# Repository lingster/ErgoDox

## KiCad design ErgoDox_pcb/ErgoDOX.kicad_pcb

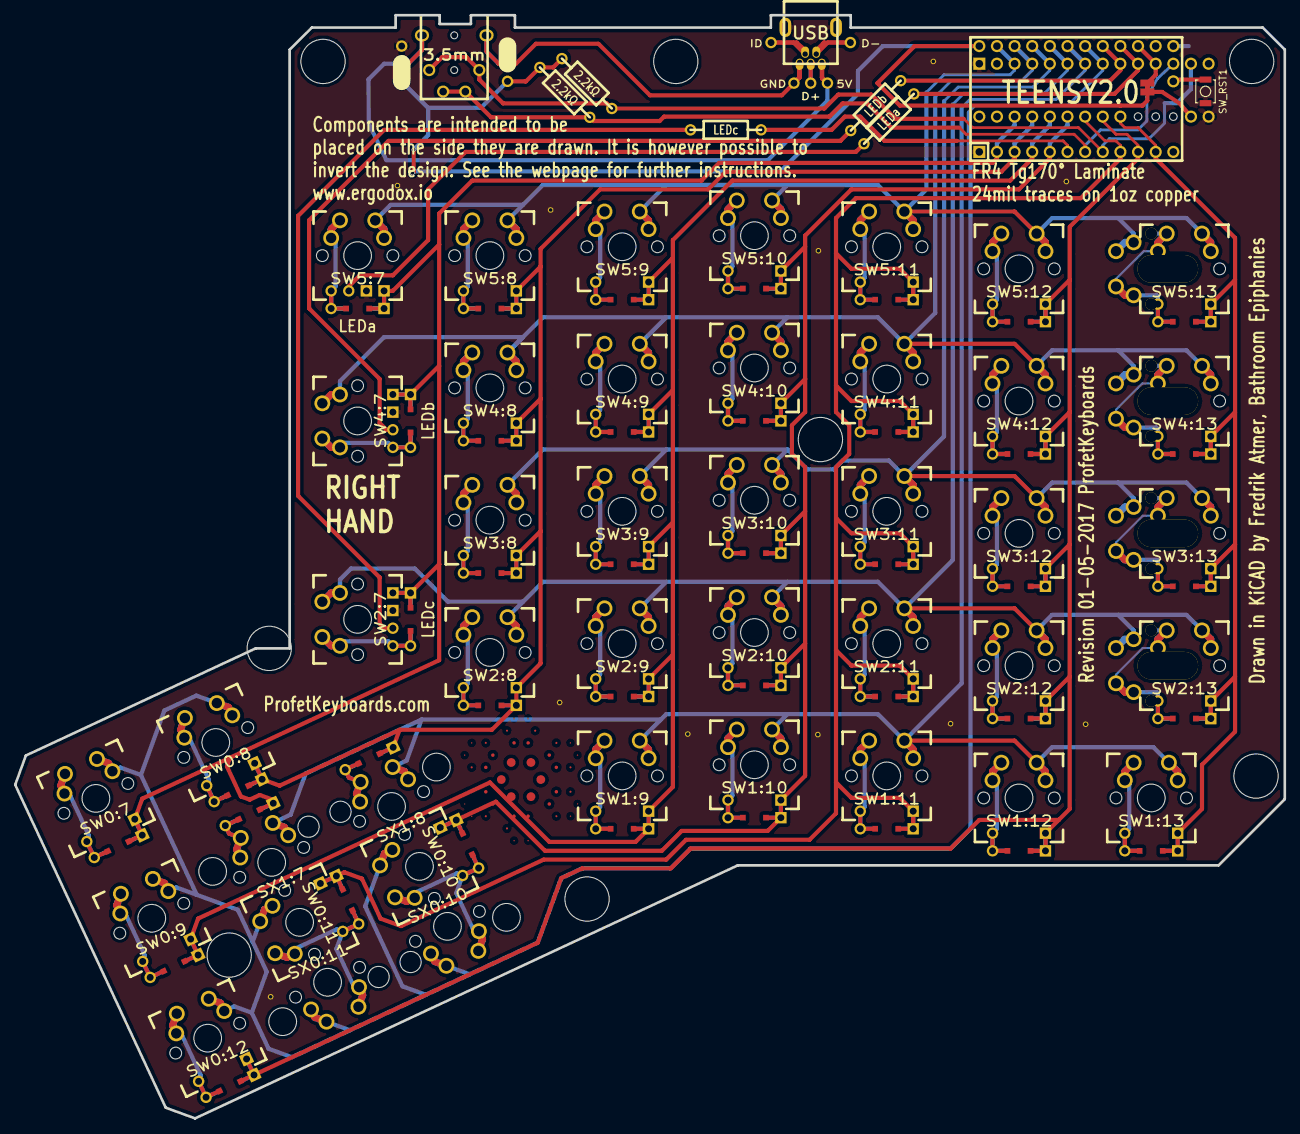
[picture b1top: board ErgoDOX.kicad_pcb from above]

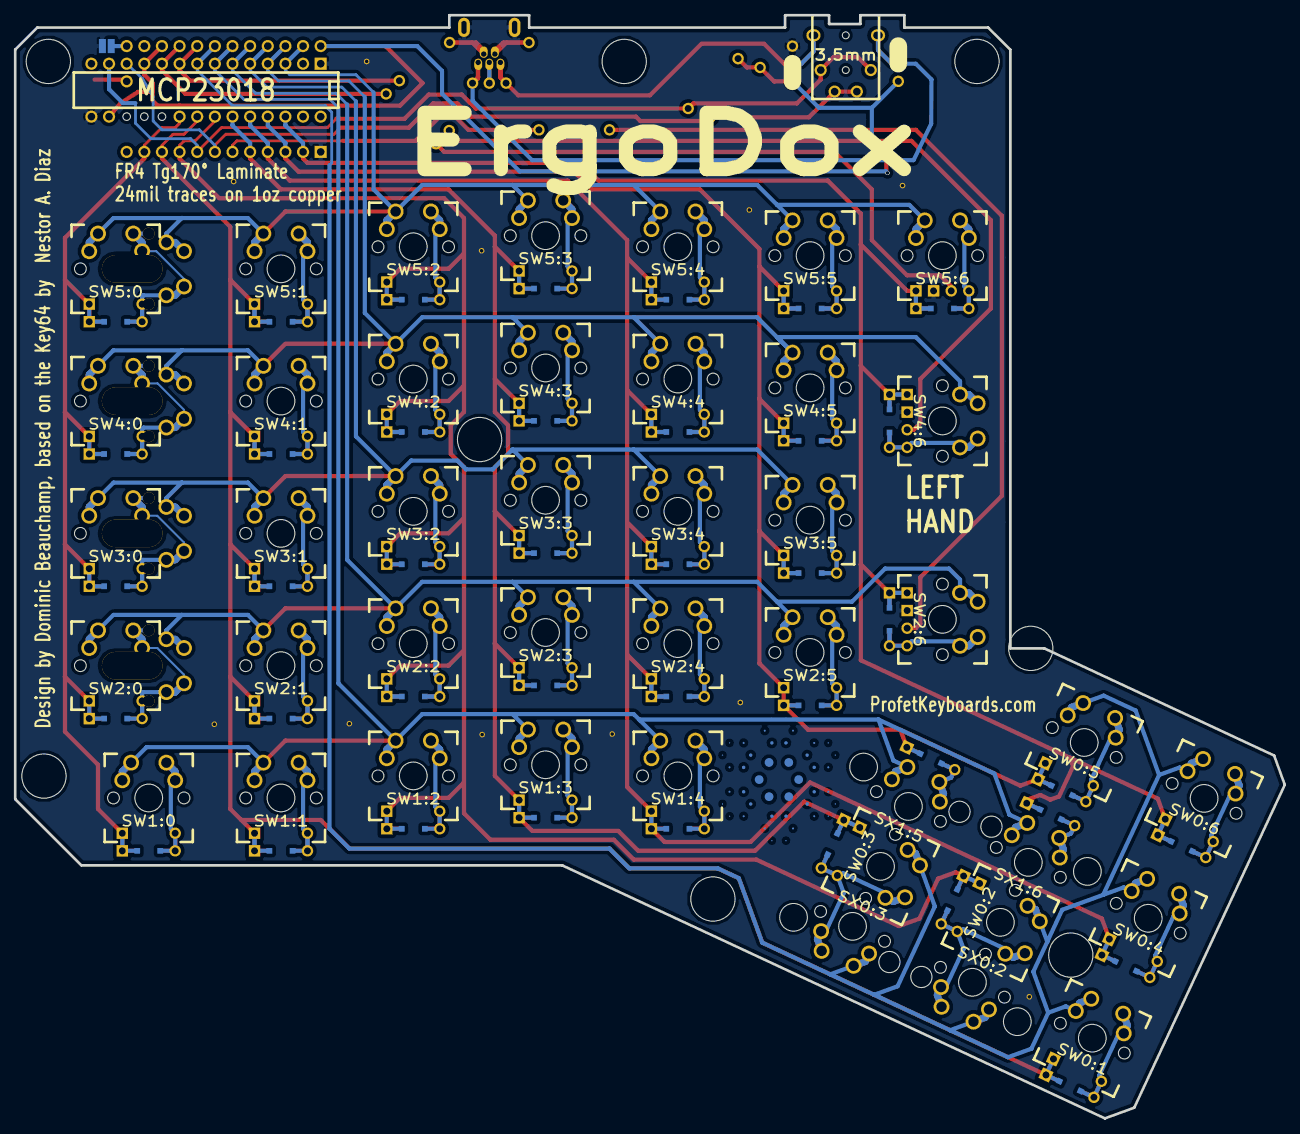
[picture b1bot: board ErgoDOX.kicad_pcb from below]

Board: 2 copper layers, 182.8 x 158.9 mm, 77 parts (4 on the bottom side), 66 nets.

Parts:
D1:7, D1:8: D; DIODE
H99: MECHANICAL; ErgoDOXmech
J1: USB; USBMINImod
J2: 3.5mm; 4pin35mmAudio
J3, J4: JMP; 100PITCH1X3
JP1, JP2: JUMPER; GAP
LED_A1: LEDa; MX_LED
LED_B1: LEDb; MX_LED
LED_C1: LEDc; MX_LED
R1, R2: 2.2kΩ; RESISTOR
RA1: LEDa; RESISTOR
RB1: LEDb; RESISTOR
RC1: LEDc; RESISTOR
S1, S2: STAB200; STAB_PCB940
STAR_1: STAR_FRONT; STAR
STAR_2: STAR_BACK; STAR
STITCHING_VIA: STITCHING_VIA
STITCHING_VIA#2, STITCHING_VIA#3, STITCHING_VIA#4, STITCHING_VIA#5, STITCHING_VIA#6, STITCHING_VIA#7, STITCHING_VIA#8, STITCHING_VIA#9, STITCHING_VIA#10, STITCHING_VIA#11: STITCHING_VIA
SW0:7: SW0:6; MX_FLIP_DIODE
SW0:8: SW0:5; MX_FLIP_DIODE
SW0:9: SW0:4; MX_FLIP_DIODE
SW0:10: SW0:3; MX_FLIP_DIODE
SW0:11: SW0:2; MX_FLIP_DIODE
SW0:12: SW0:1; MX_FLIP_DIODE
SW1:9: SW1:4; MX_FLIP_DIODE
SW1:10: SW1:3; MX_FLIP_DIODE
SW1:11: SW1:2; MX_FLIP_DIODE
SW1:12: SW1:1; MX_FLIP_DIODE
SW1:13: SW1:0; MX_FLIP_DIODE
SW2:7: SW2:6; MX_FLIP_DIODE
SW2:8: SW2:5; MX_FLIP_DIODE
SW2:9: SW2:4; MX_FLIP_DIODE
SW2:10: SW2:3; MX_FLIP_DIODE
SW2:11: SW2:2; MX_FLIP_DIODE
SW2:12: SW2:1; MX_FLIP_DIODE
SW2:13: SW2:0; MX_FLIP_XX
SW3:8: SW3:5; MX_FLIP_DIODE
SW3:9: SW3:4; MX_FLIP_DIODE
SW3:10: SW3:3; MX_FLIP_DIODE
SW3:11: SW3:2; MX_FLIP_DIODE
SW3:12: SW3:1; MX_FLIP_DIODE
SW3:13: SW3:0; MX_FLIP_XX
SW4:7: SW4:6; MX_FLIP_DIODE
SW4:8: SW4:5; MX_FLIP_DIODE
SW4:9: SW4:4; MX_FLIP_DIODE
SW4:10: SW4:3; MX_FLIP_DIODE
SW4:11: SW4:2; MX_FLIP_DIODE
SW4:12: SW4:1; MX_FLIP_DIODE
SW4:13: SW4:0; MX_FLIP_XX
SW5:7: SW5:6; MX_FLIP_DIODE
SW5:8: SW5:5; MX_FLIP_DIODE
SW5:9: SW5:4; MX_FLIP_DIODE
SW5:10: SW5:3; MX_FLIP_DIODE
SW5:11: SW5:2; MX_FLIP_DIODE
SW5:12: SW5:1; MX_FLIP_DIODE
SW5:13: SW5:0; MX_FLIP_XX
SW_RST1: SWITCH_PUSH; SW_SPST_B3U-1000P
SX0:10: SX0:3; MX_FLIP
SX0:11: SX0:2; MX_FLIP
SX1:7: SX1:6; MX_FLIP
SX1:8: SX1:5; MX_FLIP
U1: TEENSY2.0; TEENSY_2.0_WITH_RESET
U2: MCP23018; DIP28_300

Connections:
/COL0: SW1:13.4, SW2:13.4, SW3:13.4, SW4:13.4, SW5:13.4, U1.11, U2.20
/COL1: SW0:12.4, SW1:12.4, SW2:12.4, SW3:12.4, SW4:12.4, SW5:12.4, U1.10, U2.21
/COL4: SW0:9.4, SW1:9.4, SW2:9.4, SW3:9.4, SW4:9.4, SW5:9.4, U1.4, U2.24
/COL5: D1:8.2, SW0:8.4, SW2:8.4, SW3:8.4, SW4:8.4, SW5:8.4, U1.3, U2.25
/COL6: D1:7.2, SW0:7.4, SW2:7.4, SW4:7.4, SW5:7.4, U1.2, U2.26
/COL10: SW0:10.4, SW1:10.4, SW2:10.4, SW3:10.4, SW4:10.4, SW5:10.4, U1.5, U2.23
/COL11: SW0:11.4, SW1:11.4, SW2:11.4, SW3:11.4, SW4:11.4, SW5:11.4, U1.9, U2.22
/LED_A: RA1.1, U1.21, U2.10
/LED_B: RB1.1, U1.22, U2.9
/LED_C: RC1.1, U1.6
/ROW0: SW0:7.1, SW0:8.1, SW0:9.1, SW0:10.1, SW0:11.1, SW0:12.1, SX0:10.1, SX0:11.1, U1.23, U2.8
/ROW1: SW1:9.1, SW1:10.1, SW1:11.1, SW1:12.1, SW1:13.1, SX1:7.1, SX1:8.1, U1.24, U2.7
/ROW2: SW2:7.1, SW2:8.1, SW2:9.1, SW2:10.1, SW2:11.1, SW2:12.1, SW2:13.1, U1.25, U2.6
/ROW3: SW3:8.1, SW3:9.1, SW3:10.1, SW3:11.1, SW3:12.1, SW3:13.1, U1.26, U2.5
/ROW4: SW4:7.1, SW4:8.1, SW4:9.1, SW4:10.1, SW4:11.1, SW4:12.1, SW4:13.1, U1.27, U2.4
/ROW5: SW5:7.1, SW5:8.1, SW5:9.1, SW5:10.1, SW5:11.1, SW5:12.1, SW5:13.1, U1.28, U2.3
/RST: SW_RST1.1, U1.16
/SCLM: J2.3, J2.5, R2.2, U1.7, U2.12
/SDAM: J2.2, J2.6, R1.2, U1.8, U2.13
GND: J1.6, J3.3, J4.3, JP2.1, LED_A1.2, LED_B1.2, LED_C1.2, STITCHING_VIA.GND, STITCHING_VIA#2.GND, STITCHING_VIA#3.GND, STITCHING_VIA#4.GND, STITCHING_VIA#5.GND, STITCHING_VIA#6.GND, STITCHING_VIA#7.GND, STITCHING_VIA#8.GND, STITCHING_VIA#9.GND, STITCHING_VIA#10.GND, STITCHING_VIA#11.GND, SW_RST1.2, U1.1, U1.18, U2.1, U2.15
unnamed: D1:7.1, SX1:7.2
unnamed: D1:8.1, SX1:8.2
unnamed: J1.1, J2.4, J4.2
unnamed: J1.5, J2.1, J3.2
unnamed: LED_A1.1, RA1.2
unnamed: LED_B1.1, RB1.2
unnamed: LED_C1.1, RC1.2
unnamed: SW0:7.2, SW0:7.3
unnamed: SW0:8.2, SW0:8.3
unnamed: SW0:9.2, SW0:9.3
unnamed: SW0:10.2, SW0:10.3, SX0:10.2
unnamed: SW0:11.2, SW0:11.3, SX0:11.2
unnamed: SW0:12.2, SW0:12.3
unnamed: SW1:9.2, SW1:9.3
unnamed: SW1:10.2, SW1:10.3
unnamed: SW1:11.2, SW1:11.3
unnamed: SW1:12.2, SW1:12.3
unnamed: SW1:13.2, SW1:13.3
unnamed: SW2:7.2, SW2:7.3
unnamed: SW2:8.2, SW2:8.3
unnamed: SW2:9.2, SW2:9.3
unnamed: SW2:10.2, SW2:10.3
unnamed: SW2:11.2, SW2:11.3
unnamed: SW2:12.2, SW2:12.3
unnamed: SW2:13.2, SW2:13.3
unnamed: SW3:8.2, SW3:8.3
unnamed: SW3:9.2, SW3:9.3
unnamed: SW3:10.2, SW3:10.3
unnamed: SW3:11.2, SW3:11.3
unnamed: SW3:12.2, SW3:12.3
unnamed: SW3:13.2, SW3:13.3
unnamed: SW4:7.2, SW4:7.3
unnamed: SW4:8.2, SW4:8.3
unnamed: SW4:9.2, SW4:9.3
unnamed: SW4:10.2, SW4:10.3
unnamed: SW4:11.2, SW4:11.3
unnamed: SW4:12.2, SW4:12.3
unnamed: SW4:13.2, SW4:13.3
unnamed: SW5:7.2, SW5:7.3
unnamed: SW5:8.2, SW5:8.3
unnamed: SW5:9.2, SW5:9.3
unnamed: SW5:10.2, SW5:10.3
unnamed: SW5:11.2, SW5:11.3
unnamed: SW5:12.2, SW5:12.3
unnamed: SW5:13.2, SW5:13.3
VCC: J3.1, J4.1, JP1.1, R1.1, R2.1, U1.20, U1.29, U2.11, U2.16

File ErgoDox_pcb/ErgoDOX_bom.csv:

Reference, Value, Footprint, Datasheet
"RC1","LEDc","",""
"LED_C1","LEDc","",""
"LED_B1","LEDb","",""
"RB1","LEDb","",""
"RA1","LEDa","",""
"LED_A1","LEDa","",""
"H99","MECHANICAL","",""
"SW1:11","SW1:2","",""
"SW1:10","SW1:3","",""
"SW0:9","SW0:4","",""
"SW0:8","SW0:5","",""
"SW0:12","SW0:1","",""
"SW0:11","SW0:2","",""
"SW2:12","SW2:1","",""
"SW2:13","SW2:0","",""
"SW1:13","SW1:0","",""
"SW3:13","SW3:0","",""
"SW2:7","SW2:6","",""
"SW2:8","SW2:5","",""
"SW2:9","SW2:4","",""
"SW2:11","SW2:2","",""
"SW1:12","SW1:1","",""
"SW3:8","SW3:5","",""
"SW3:9","SW3:4","",""
"SW3:10","SW3:3","",""
"SW3:11","SW3:2","",""
"SW3:12","SW3:1","",""
"SW4:13","SW4:0","",""
"SW4:9","SW4:4","",""
"SW4:10","SW4:3","",""
"SW4:11","SW4:2","",""
"SW4:12","SW4:1","",""
"SW4:8","SW4:5","",""
"SW4:7","SW4:6","",""
"SW0:7","SW0:6","",""
"U2","MCP23018","",""
"R2","2.2kΩ","",""
"R1","2.2kΩ","",""
"J2","3.5mm","",""
"J3","JMP","",""
"J4","JMP","",""
"U1","TEENSY2.0","",""
"SW2:10","SW2:3","",""
"J1","USB","",""
"SW5:13","SW5:0","",""
"SW5:9","SW5:4","",""
"SW5:10","SW5:3","",""
"SW5:11","SW5:2","",""
"SW5:12","SW5:1","",""
"SW5:8","SW5:5","",""
"SW5:7","SW5:6","",""
"SX1:8","SX1:5","",""
"SX1:7","SX1:6","",""
"SX0:10","SX0:3","",""
"SX0:11","SX0:2","",""
"D1:7","D","",""
"D1:8","D","",""
"SW1:9","SW1:4","",""
"SW0:10","SW0:3","",""
"JP2","JUMPER","",""
"JP1","JUMPER","",""
"S1","STAB200","",""
"S2","STAB200","",""
"SW_RST1","SWITCH_PUSH","Buttons_Switches_SMD:SW_SPST_B3U-1000P",""

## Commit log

2019-09-20 Ling's Changes
    Added SCAD drawings for case
    Made switches through hole
2019-09-20 updated rescue files
